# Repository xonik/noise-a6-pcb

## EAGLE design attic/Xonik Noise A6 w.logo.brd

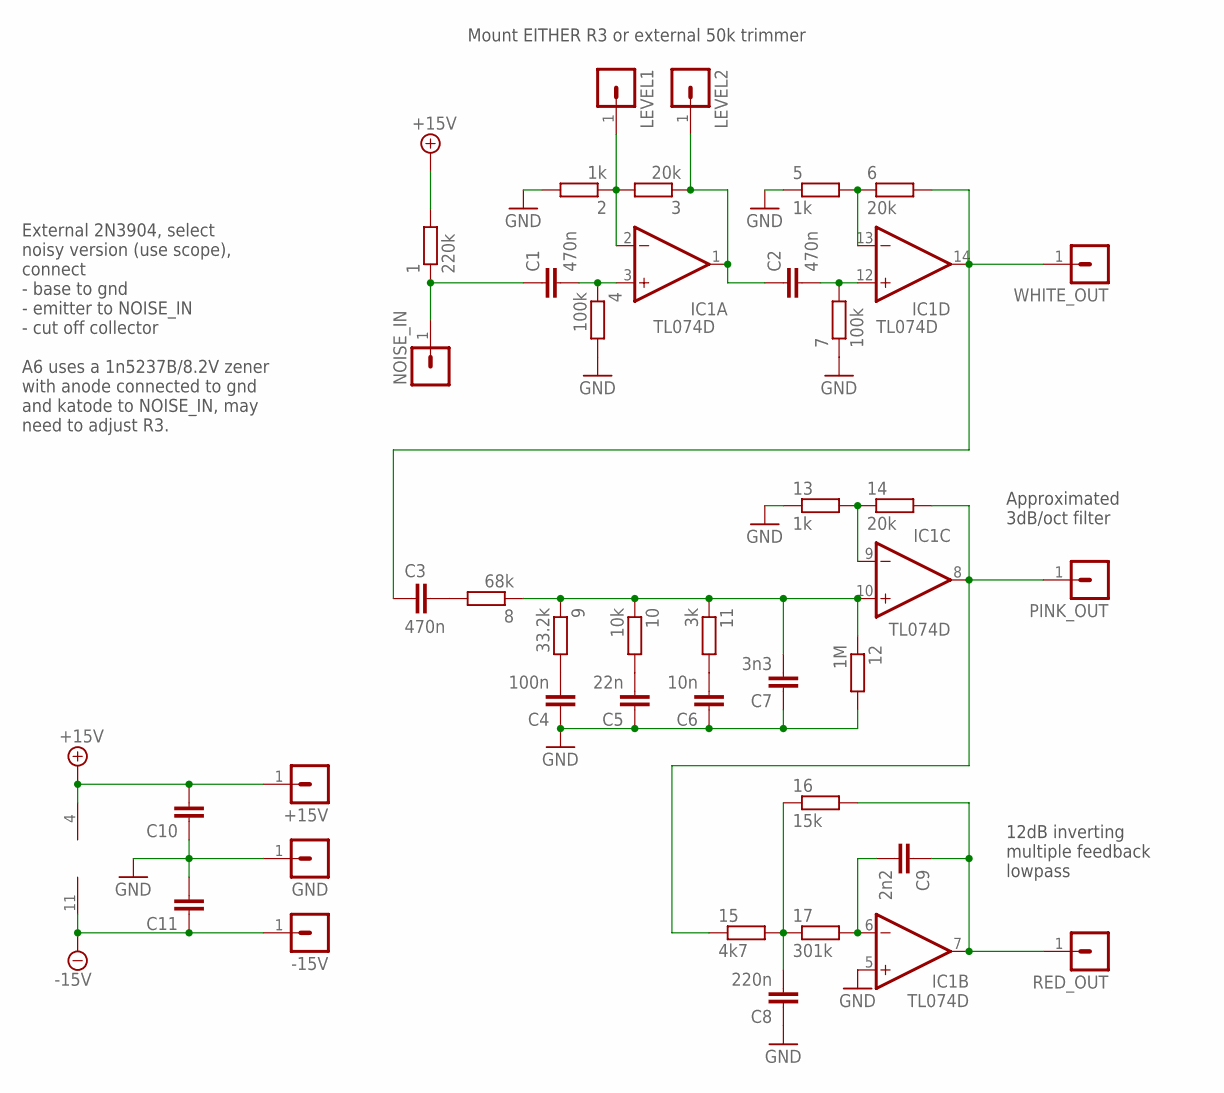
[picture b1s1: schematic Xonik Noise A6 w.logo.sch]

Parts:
1: 220k; R0805
2, 5, 13: 1k; R0805
3, 6, 14: 20k; R0805
4, 7: 100k; R0805
8: 68k; R0805
9: 33.2k; R0805
10: 10k; R0805
11: 3k; R0805
12: 1M; R0805
15: 4k7; R0805
16: 15k; R0805
17: 301k; R0805
+15V: MA01-1JP; SIP-PIN01-1J
-15V: MA01-1JP; SIP-PIN01-1J
C1, C2, C3: 470n; C0805
C4: 100n; C0805
C5: 22n; C0805
C6: 10n; C0805
C7: 3n3; C0805
C8: 220n; C0805
C9: 2n2; C0805
C10, C11: C-EUC0603; C0603
GND: MA01-1JP; SIP-PIN01-1J
IC1: TL074D; SO14
LEVEL1, LEVEL2: MA01-1JP; SIP-PIN01-1J
NOISE_IN: MA01-1JP; SIP-PIN01-1J
PINK_OUT: MA01-1JP; SIP-PIN01-1J
RED_OUT: MA01-1JP; SIP-PIN01-1J
WHITE_OUT: MA01-1JP; SIP-PIN01-1J

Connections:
+15V: 1.2, +15V.1, C10.2, IC1.4 (V+)
-15V: -15V.1, C11.1, IC1.11 (V-)
GND: 2.2, 4.2, 5.1, 7.1, 12.2, 13.1, C4.1, C5.1, C6.1, C7.1, C8.1, C10.1, C11.2, GND.1, IC1.5 (+IN)
unnamed: 2.1, 3.2, IC1.2 (-IN), LEVEL1.1
unnamed: 5.2, 6.1, IC1.13 (-IN)
unnamed: 13.2, 14.1, IC1.9 (-IN)
unnamed: 9.2, C4.2
unnamed: 10.2, C5.2
unnamed: 11.2, C6.2
unnamed: 1.1, C1.1, NOISE_IN.1
unnamed: 4.1, C1.2, IC1.3 (+IN)
unnamed: 3.1, C2.1, IC1.1 (OUT), LEVEL2.1
unnamed: 7.2, C2.2, IC1.12 (+IN)
unnamed: 6.2, C3.1, IC1.14 (OUT), WHITE_OUT.1
unnamed: 8.1, 9.1, 10.1, 11.1, 12.1, C7.2, IC1.10 (+IN)
unnamed: 8.2, C3.2
unnamed: 14.2, 15.1, IC1.8 (OUT), PINK_OUT.1
unnamed: 15.2, 16.1, 17.1, C8.2
unnamed: 17.2, C9.2, IC1.6 (-IN)
unnamed: 16.2, C9.1, IC1.7 (OUT), RED_OUT.1

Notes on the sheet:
Mount EITHER R3 or external 50k trimmer
Approximated 3dB/oct filter
12dB inverting multiple feedback lowpass
External 2N3904, select noisy version (use scope), connect - base to gnd - emitter to NOISE_IN - cut off collector A6 uses a 1n5237B/8.2V zener with anode connected to gnd and katode to NOISE_IN, may need to adjust R3.

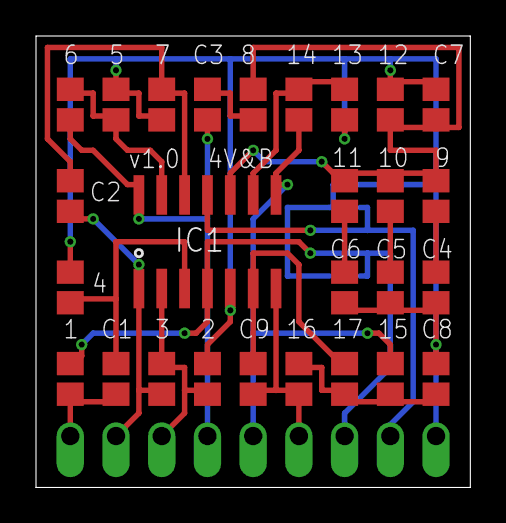
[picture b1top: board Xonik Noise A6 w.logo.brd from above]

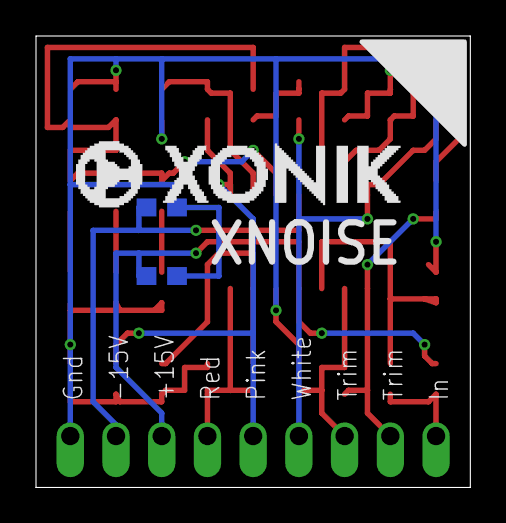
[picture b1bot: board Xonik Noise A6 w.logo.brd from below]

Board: 2 copper layers, 24.1 x 25.1 mm, 38 parts (2 on the bottom side), 20 nets.

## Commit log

2017-10-08 Xonik Noise A6 - Andromeda A6 based noise circuit with some values changed
2017-10-09 Routing completed except for error checking.
2018-01-27 new versions
2020-02-15 Version 2 with screw hole, on board noisy tranny, fixed entry point for smd resistor paths etc
2020-02-17 Vector xonik logo
2020-02-18 Added parts list for smd assembly
2020-02-20 Removed default gain resistor and added doc for trimmer
2020-02-22 Changed to logo-as-component
2020-02-26 Added git ignore
2020-03-02 Added working bom and gerber
2020-03-03 Added comment about trimmer
2020-06-21 Changed recommended external trimmer for 50k to 100k to be able to reach a high enough amplitude
2023-03-13 Working on 12v version with 0603 res
2023-03-13 Version 2.1 12V completed I think
2023-03-13 Tiny tweaks
2023-03-14 Angled corner. Finally.
2024-05-26 Cleanup
